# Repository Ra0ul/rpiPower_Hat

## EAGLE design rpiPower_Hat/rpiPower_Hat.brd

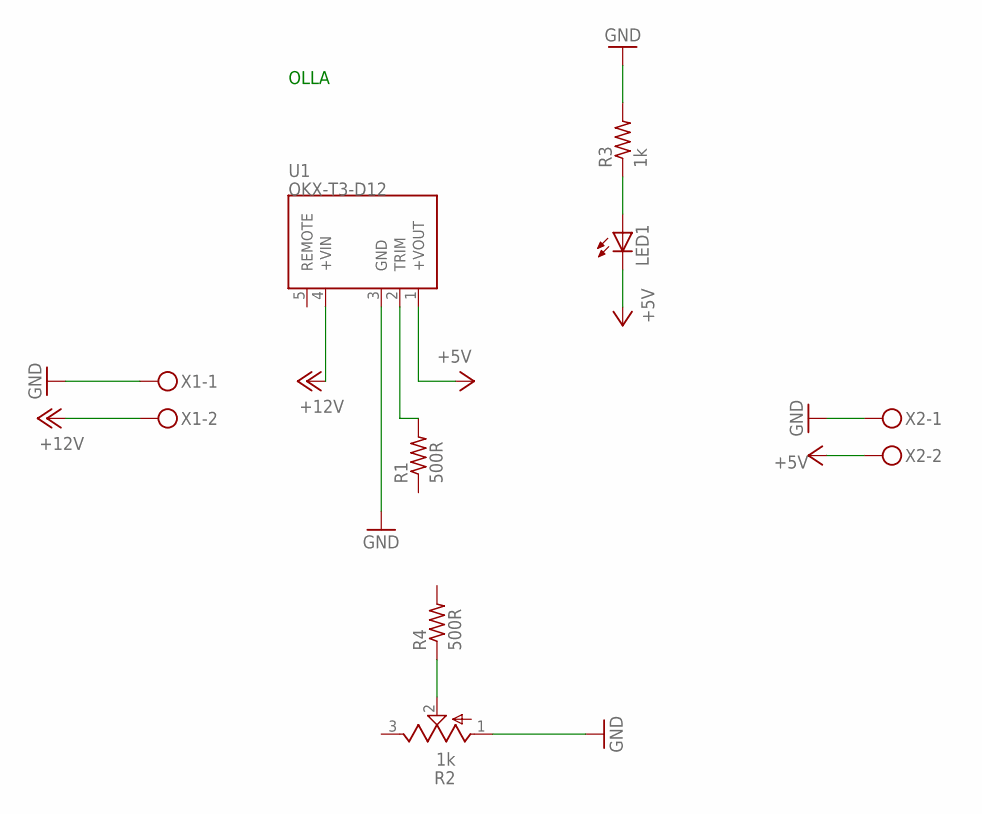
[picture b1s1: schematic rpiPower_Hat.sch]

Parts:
LED1: LEDCHIP-LED0603; CHIP-LED0603
R1, R4: 500R; R0603
R2: 1k; RTRIM3296W
R3: 1k; R0603
U1: OKX-T3-D12
X1, X2: MKDSN1,5/2-5,08

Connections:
+5V: LED1.C, U1.1 (+VOUT), X2.2
+12V: U1.4 (+VIN), X1.2
GND: R2.1 (A), R3.2, U1.3 (GND), X1.1, X2.1
unnamed: R1.2, U1.2 (TRIM)
unnamed: R2.2 (S), R4.1
unnamed: LED1.A, R3.1

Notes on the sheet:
OLLA

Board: 2 copper layers, 8 parts (0 on the bottom side), 6 nets, no tracks yet.

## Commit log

2021-04-18 first upload
2021-04-18 make new board
